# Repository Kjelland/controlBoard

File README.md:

# controlBoard
Hardware and software for the winch controller

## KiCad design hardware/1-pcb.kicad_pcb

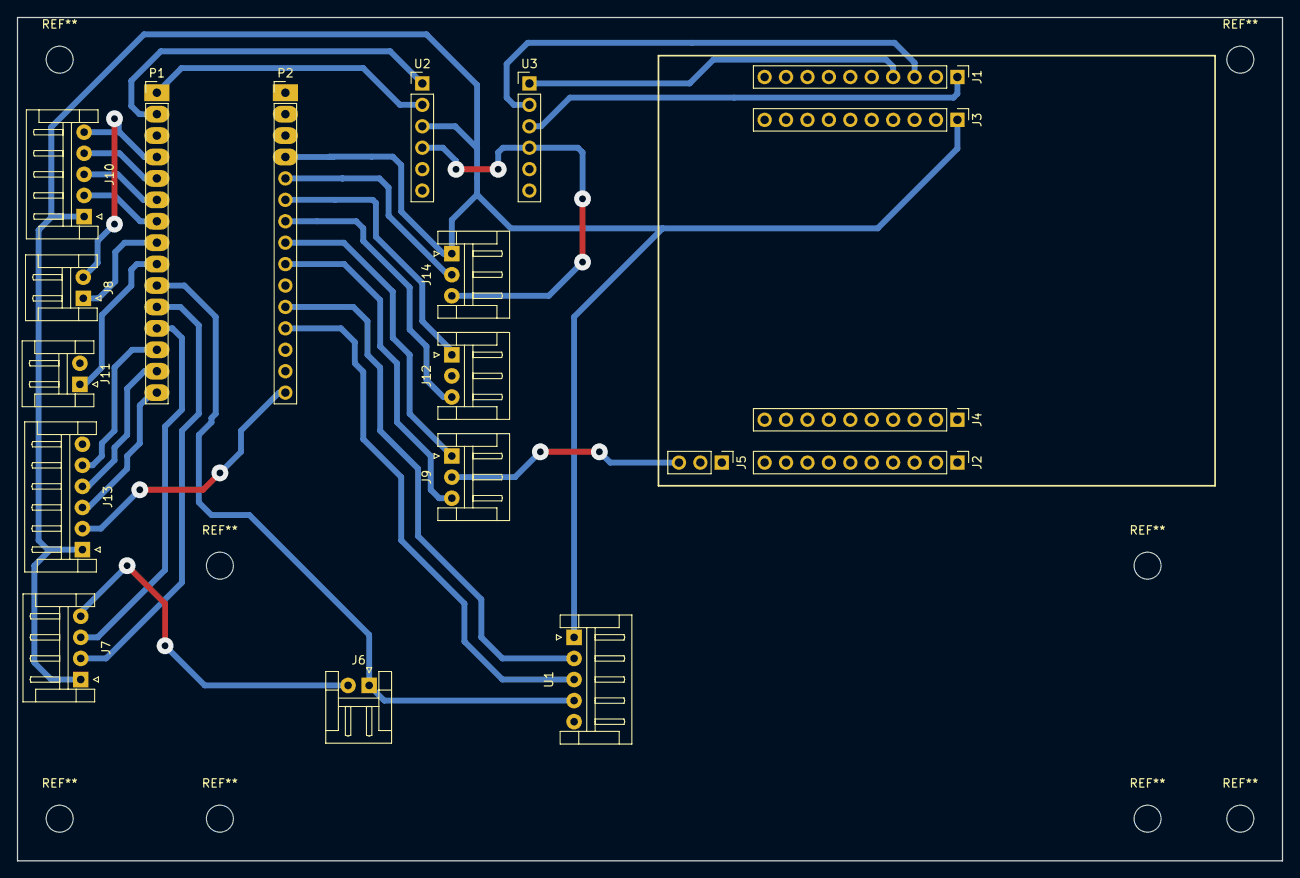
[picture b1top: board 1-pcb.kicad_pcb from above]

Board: 2 copper layers, 150.0 x 100.0 mm, 19 parts (0 on the bottom side), 26 nets.

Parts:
J1: TI_BOOSTER_40_J1; Pin_Header_Straight_1x10_Pitch2.54mm
J2: TI_BOOSTER_40_J2; Pin_Header_Straight_1x10_Pitch2.54mm
J3: TI_BOOSTER_40_J3; Pin_Header_Straight_1x10_Pitch2.54mm
J4: TI_BOOSTER_40_J4; Pin_Header_Straight_1x10_Pitch2.54mm
J5: CONN_3; Pin_Header_Straight_1x03_Pitch2.54mm
J6: push button; JST_EH_S02B-EH_02x2.50mm_Angled
J7: display; JST_EH_S04B-EH_04x2.50mm_Angled
J8, J11: led; JST_EH_S02B-EH_02x2.50mm_Angled
J9, J12: 2 pos switch; JST_EH_S03B-EH_03x2.50mm_Angled
J10: encoder; JST_EH_S05B-EH_05x2.50mm_Angled
J13: spi; JST_EH_S06B-EH_06x2.50mm_Angled
J14: hallEffectEncoder; JST_EH_S03B-EH_03x2.50mm_Angled
P1: Digital; Socket_Strip_Straight_1x15_Pitch2.54mm
P2: Analog; Socket_Strip_Straight_1x15_Pitch2.54mm
U1: Joystick; JST_EH_S05B-EH_05x2.50mm_Angled
U2: levelConverter high side; Pin_Header_Straight_1x06_Pitch2.54mm
U3: levelConverter low side; Socket_Strip_Straight_1x06_Pitch2.54mm

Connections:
+3V3: J1.1, U3.3
+5V: J3.1, J7.1, J10.1, J13.1, J14.1, P2.4, U1.1, U2.3
/0(Rx): P1.2, U2.1
/1(Tx): P1.1, U2.2
/2: J10.4, P1.5
/3(**): J10.3, P1.6
/4: J10.2, P1.7
/5(**): J8.1, P1.8
/6(**): J11.1, P1.9
/7: J6.1, P1.10, U1.4
/8: J7.2, P1.11
/9(**): J7.3, P1.12
/10(**/SS): J13.5, P1.13
/11(**/MOSI): J13.4, P1.14
/12(MISO): J13.3, P1.15
/13(SCK): J13.2, P2.15
/A0: P2.12, U1.3
/A1: P2.11, U1.2
/A3: J9.3, P2.9
/A4: J9.1, P2.8
/A5: J12.3, P2.7
/A6: J12.1, P2.6
/A7: J14.2, P2.5
GND: J2.1, J3.2, J5.2, J5.3, J6.2, J7.4, J8.2, J9.2, J10.5, J11.2, J12.2, J13.6, J14.3, P1.4, P2.2, U1.5, U2.4, U3.4
RxD: J1.3, U3.2
TxD: J1.4, U3.1
